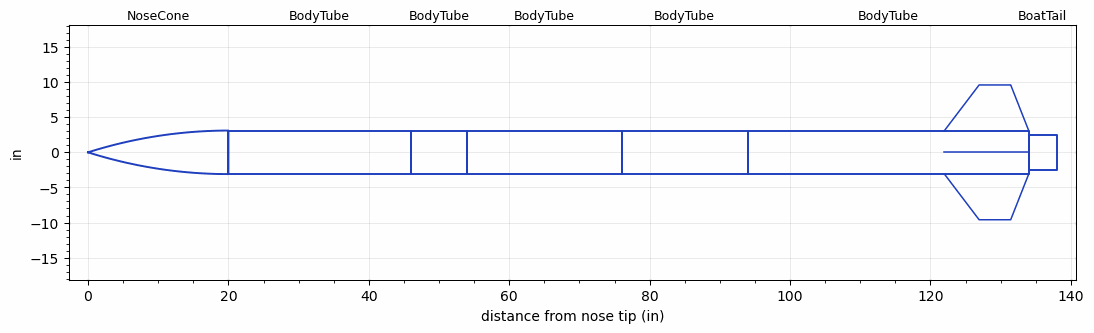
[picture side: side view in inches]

<RASAeroDocument>
 <FileVersion>2</FileVersion>
 <RocketDesign>
  <NoseCone>
   <Length>20</Length>
   <Diameter>6.2</Diameter>
   <Shape>Tangent Ogive</Shape>
   <Location>0</Location>
  </NoseCone>
  <BodyTube>
   <Length>25.9999</Length>
   <Diameter>6.2</Diameter>
   <Location>20</Location>
  </BodyTube>
  <BodyTube>
   <Length>8</Length>
   <Diameter>6.2</Diameter>
   <Location>45.9999</Location>
  </BodyTube>
  <BodyTube>
   <Length>22</Length>
   <Diameter>6.2</Diameter>
   <Location>53.9999</Location>
  </BodyTube>
  <BodyTube>
   <Length>18</Length>
   <Diameter>6.2</Diameter>
   <Location>75.9998</Location>
  </BodyTube>
  <BodyTube>
   <Length>39.9999</Length>
   <Diameter>6.2</Diameter>
   <RailGuideDiameter>0.621</RailGuideDiameter>
   <RailGuideHeight>0.6845</RailGuideHeight>
   <Location>93.9998</Location>
   <Fin>
    <Count>4</Count>
    <Chord>12</Chord>
    <Span>6.5</Span>
    <SweepDistance>4.937</SweepDistance>
    <TipChord>4.5</TipChord>
    <Thickness>0.125</Thickness>
    <Location>12</Location>
    <AirfoilSection>Rounded</AirfoilSection>
   </Fin>
  </BodyTube>
  <BoatTail>
   <Length>4</Length>
   <Diameter>5</Diameter>
   <RearDiameter>5</RearDiameter>
   <Location>133.9997</Location>
  </BoatTail>
  <Surface>Sheet Metal</Surface>
  <CD>0</CD>
  <ModifiedBarrowman>False</ModifiedBarrowman>
  <Turbulence>False</Turbulence>
  <UseBooster1>False</UseBooster1>
  <UseBooster2>False</UseBooster2>
 </RocketDesign>
 <LaunchSite>
  <Altitude>2870.735</Altitude>
  <Pressure>26.9525</Pressure>
  <RodAngle>5</RodAngle>
  <RodLength>163.9997</RodLength>
  <Temperature>48.7625</Temperature>
  <WindSpeed>15</WindSpeed>
 </LaunchSite>
 <Recovery>
  <Altitude1>1476.378</Altitude1>
  <Altitude2>0</Altitude2>
  <DeviceType1>Parachute</DeviceType1>
  <DeviceType2>None</DeviceType2>
  <Event1>True</Event1>
  <Event2>False</Event2>
  <Size1>91.1998</Size1>
  <Size2>0</Size2>
  <EventType1>Altitude</EventType1>
  <EventType2>None</EventType2>
  <CD1>2.17</CD1>
  <CD2>0</CD2>
 </Recovery>
 <SimulationList>
  <Simulation>
   <SustainerEngine>N3800-LW  (LR)</SustainerEngine>
   <SustainerLaunchWt>90.2738</SustainerLaunchWt>
   <SustainerCG>83.6063</SustainerCG>
   <SustainerIgnitionDelay>0</SustainerIgnitionDelay>
   <Booster1SeparationDelay>0</Booster1SeparationDelay>
   <Booster1IgnitionDelay>0</Booster1IgnitionDelay>
   <IncludeBooster1>False</IncludeBooster1>
   <Booster2Delay>0</Booster2Delay>
   <IncludeBooster2>False</IncludeBooster2>
  </Simulation>
 </SimulationList>
</RASAeroDocument>
